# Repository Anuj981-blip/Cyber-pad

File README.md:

---

# CyberPad — 3×3 Macropad

A compact 9-key macropad with rotary encoder, OLED display, and three switchable profiles (Productivity, Gaming, Media). Built around the Seeed XIAO RP2040 and powered by KMK firmware.

## Features

- **9 MX-style switches** in a 3×3 matrix
- **Rotary encoder** with push-button for layer-aware actions
- **128×32 SSD1306 OLED** showing active profile icon, profile name, and current layer
- **3 profiles** (Productivity / Gaming / Media), each with 2 layers
- **Profile switching** via top-row chord (hold keys 1+2+3 simultaneously)
- **Per-profile boot animation** and profile transition flash on the OLED
- 3D-printed enclosure with heat-set inserts

---

## Screenshots & Renders

----

### Schematic

**Pin mapping (Seeed XIAO RP2040):**

| Signal  | XIAO Pin | GPIO  | Notes                |
|---------|----------|-------|----------------------|
| Col 0   | D0       | GP26  | SW1 / SW4 / SW7      |
| Col 1   | D1       | GP27  | SW2 / SW5 / SW8      |
| Col 2   | D2       | GP28  | SW3 / SW6 / SW9      |
| Row 0   | D3       | GP29  | SW1 / SW2 / SW3      |
| Row 1   | D6       | GP0   | SW4 / SW5 / SW6      |
| Row 2   | D7       | GP1   | SW7 / SW8 / SW9      |
| SDA     | D4       | GP6   | OLED SDA             |
| SCL     | D5       | GP7   | OLED SCL             |
| Enc CLK | D9       | GP3   | Encoder A            |
| Enc DT  | D10      | GP4   | Encoder B            |
| Enc SW  | D8       | GP2   | Encoder push-button  |

---

### PCB Layout

- 2-layer PCB, 80 × 80 mm
- MX switch footprints with 1N4148 through-hole diode per switch (COL2ROW)
- EC11 rotary encoder footprint
- 4× M3 mounting holes (corner, 4 mm from edge)
- JST connector for optional battery

---

### Case (3D)
Top:
Bottom:

Assembled:

- Two-part snap/screw enclosure
- Top shell: switch plate integrated, 1.6 mm switch travel clearance
- Bottom shell: 4× M3×5×4 mm heat-set insert bosses
- OLED window cut-out, encoder knob cutout, USB-C access port
- Designed in Fusion 360, exported as STEP

---

## Bill of Materials

A fully itemized list of all components required to build a CyberPad.

| Qty | Item                              | Notes                                  |
|-----|-----------------------------------|----------------------------------------|
| ×1  | Custom PCB                        | See `PCB/` and `production/gerbers.zip`|
| ×1  | 3D-Printed Case (Top + Bottom)    | See `CAD/Top.STEP` & `CAD/Bottom.STEP` |
| ×1  | Seeed XIAO RP2040                 | Main microcontroller                   |
| ×1  | 0.91" OLED Display (SSD1306 I2C)  | 128×32, I2C address 0x3C               |
| ×1  | EC11 Rotary Encoder               | With push-button, 20 detents           |
| ×9  | MX-Style Switches                 | 5-pin or 3-pin (PCB-mount)             |
| ×9  | White Keycaps                     | 1U                                     |
| ×9  | Through-hole 1N4148 Diodes        | SOD-27 / DO-35 glass                   |
| ×4  | M3×16 mm Screws                   | Phillips or hex socket                 |
| ×4  | M3×5×4 mm Heat-set Inserts        | For bottom shell bosses                |

---

## Firmware

**Runtime:** CircuitPython 9.x + KMK

**Required libraries (copy to `CIRCUITPY/lib/`):**

```
kmk/
adafruit_displayio_ssd1306.mpy
adafruit_display_text/
```

**Flash instructions:**

1. Download CircuitPython `.uf2` for XIAO RP2040 from [circuitpython.org](https://circuitpython.org/board/seeeduino_xiao_rp2040/)
2. Hold BOOT, plug in USB → drag `.uf2` to the `RPI-RP2` drive
3. Copy the `lib/` folder and `main.py` to `CIRCUITPY/`
4. Device reboots automatically — OLED shows boot animation

**Profiles:**

| Profile      | Layer 0                     | Layer 1                    | Encoder CW/CCW        |
|--------------|-----------------------------|----------------------------|-----------------------|
| Productivity | Copy/Paste/Undo, Save/Find  | Redo/Cut/Dup, Print/Open   | Undo / Redo           |
| Gaming       | ESC, 1–5, R/B/G             | F1–F10                     | Page Up / Page Down   |
| Media        | Play/Prev/Next, Vol±        | Screenshots, Window snap   | Vol+ / Vol−           |

Switch profiles by holding the entire top row (keys 1+2+3) simultaneously.

---

## Repository Structure

```
CyberPad/
├── README.md
├── CAD/
│   ├── assembled-model.STEP
│   ├── Top.STEP
│   └── Bottom.STEP
├── PCB/
│   ├── cyberpad.kicad_pro
│   ├── cyberpad.kicad_sch
│   └── cyberpad.kicad_pcb
├── Firmware/
│   └── main.py
└── production/
    ├── gerbers.zip
    ├── Top.STEP
    ├── Bottom.STEP
    └── main.py
```

---
AI was used to correct the errors in the code

---

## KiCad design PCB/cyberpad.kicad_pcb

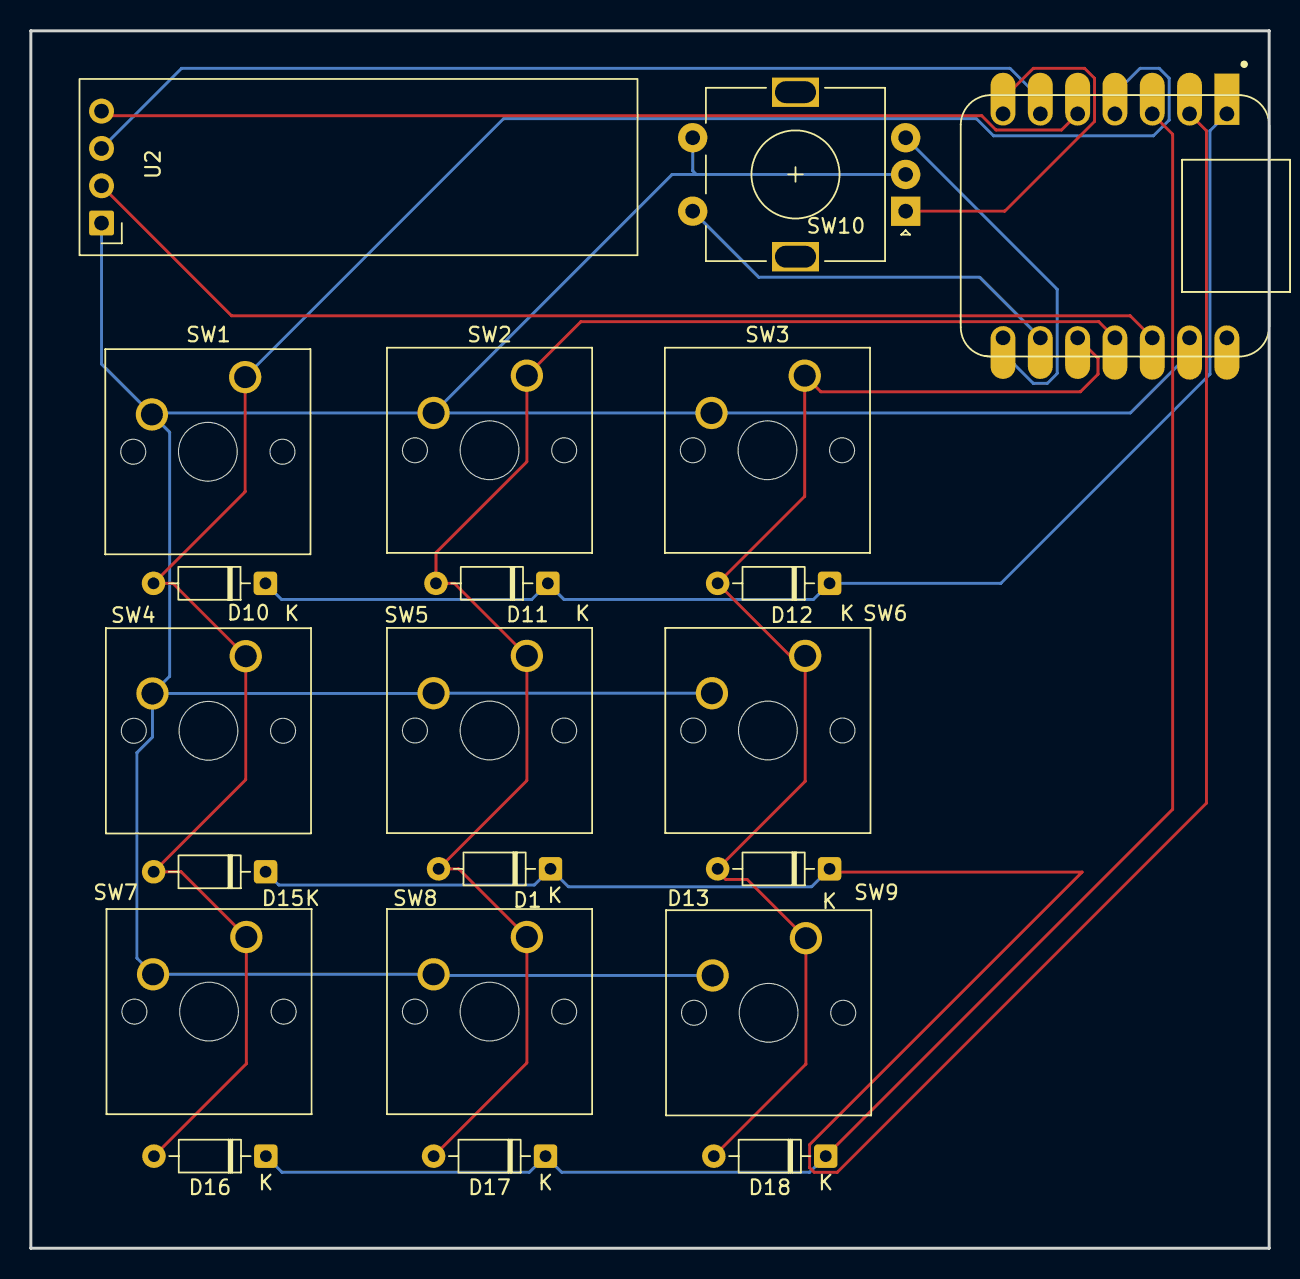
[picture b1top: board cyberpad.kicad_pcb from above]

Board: 2 copper layers, 84.3 x 82.9 mm, 21 parts (0 on the bottom side), 13 nets.

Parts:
D1, D10, D11, D12, D13, D15, D16, D17, D18: 1N4148; D_DO-35_SOD27_P7.62mm_Horizontal
SW1, SW2, SW3, SW4, SW5, SW6, SW7, SW8, SW9: SW_Push; SW_Cherry_MX_1.00u_PCB
SW10: RotaryEncoder_Switch; RotaryEncoder_Alps_EC11E-Switch_Vertical_H20mm
U1: MOUDLE-SEEEDUINO-XIAO; XIAO-Generic-Hybrid-14P-2.54-21X17.8MM
U2: ER_OLEDM0.91_1x-I2C

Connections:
/Col1: D10.2 (A), D15.2 (A), D16.2 (A), SW1.1, SW4.1, SW7.1, U1.4 (PA11_A3_D3)
/Col2: D1.2 (A), D11.2 (A), D17.2 (A), SW2.1, SW5.1, SW8.1, U1.11 (PA6_A10_D10_MOSI)
/Col3: D12.2 (A), D13.2 (A), D18.2 (A), SW3.1, SW6.1, SW9.1, U1.10 (PA5_A9_D9_MISO)
/OLED-SCL: U1.6 (PA9_A5_D5_SCL), U2.3 (SCL)
/OLED-SDA: U1.5 (PA8_A4_D4_SDA), U2.4 (SDA)
/Row1: D10.1 (K), D11.1 (K), D12.1 (K), U1.1 (PA02_A0_D0)
/Row2: D1.1 (K), D13.1 (K), D15.1 (K), U1.2 (PA4_A1_D1)
/Row3: D16.1 (K), D17.1 (K), D18.1 (K), U1.3 (PA10_A2_D2)
/SW10-A: SW10.A, U1.7 (PB08_A6_D6_TX)
/SW10-B: SW10.B, U1.8 (PB09_A7_D7_RX)
/SW10-S1: SW10.S2, U1.9 (PA7_A8_D8_SCK)
GND: SW1.2, SW2.2, SW3.2, SW4.2, SW5.2, SW6.2, SW7.2, SW8.2, SW9.2, SW10.C, SW10.S1, U1.13 (GND), U2.1 (GND)
unnamed: U1.12 (3V3), U2.2 (VCC)

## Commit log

2026-06-10 Update README to reflect project name change
    Remove old project name and keep the updated title.
